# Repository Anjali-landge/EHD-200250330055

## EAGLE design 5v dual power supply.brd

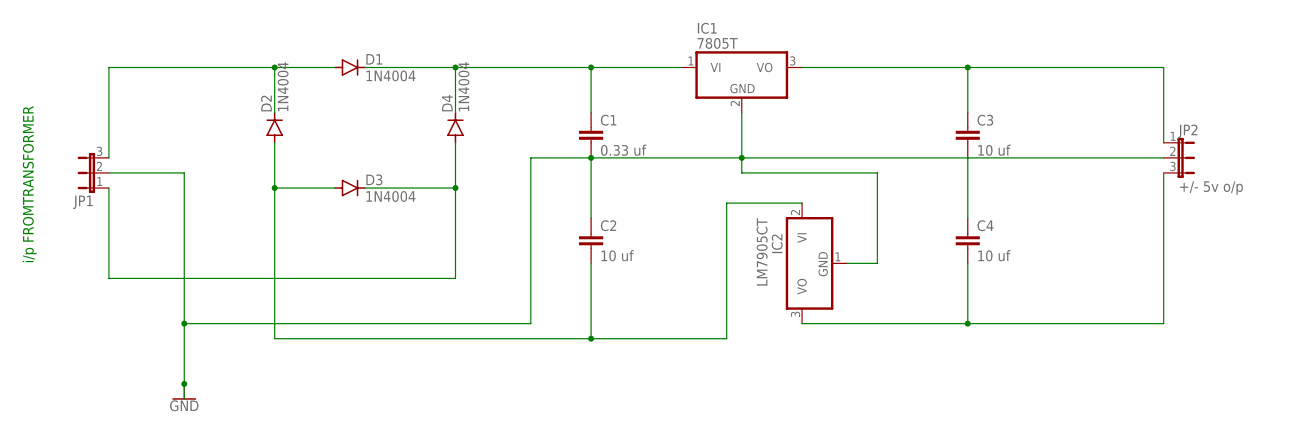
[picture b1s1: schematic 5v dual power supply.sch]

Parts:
C1: 0.33 uf; C2.5-3
C2, C3, C4: 10 uf; C2.5-3
D1, D2, D3, D4: 1N4004; DO41-10
IC1: 7805T; TO220H
IC2: LM7905CT; TO220H
JP1: JP2E; JP2
JP2: +/- 5v o/p; JP2

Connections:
GND: C1.2, C2.1, IC1.2 (GND), IC2.1 (GND), JP1.2, JP2.2
unnamed: C1.1, D1.C, D4.C, IC1.1 (VI)
unnamed: D3.C, D4.A, JP1.1
unnamed: D1.A, D2.C, JP1.3
unnamed: C2.2, D2.A, D3.A, IC2.2 (VI)
unnamed: C3.1, IC1.3 (VO), JP2.1
unnamed: C3.2, C4.1
unnamed: C4.2, IC2.3 (VO), JP2.3

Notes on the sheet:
i/p FROMTRANSFORMER

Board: 2 copper layers, 12 parts (0 on the bottom side), 8 nets, no tracks yet.

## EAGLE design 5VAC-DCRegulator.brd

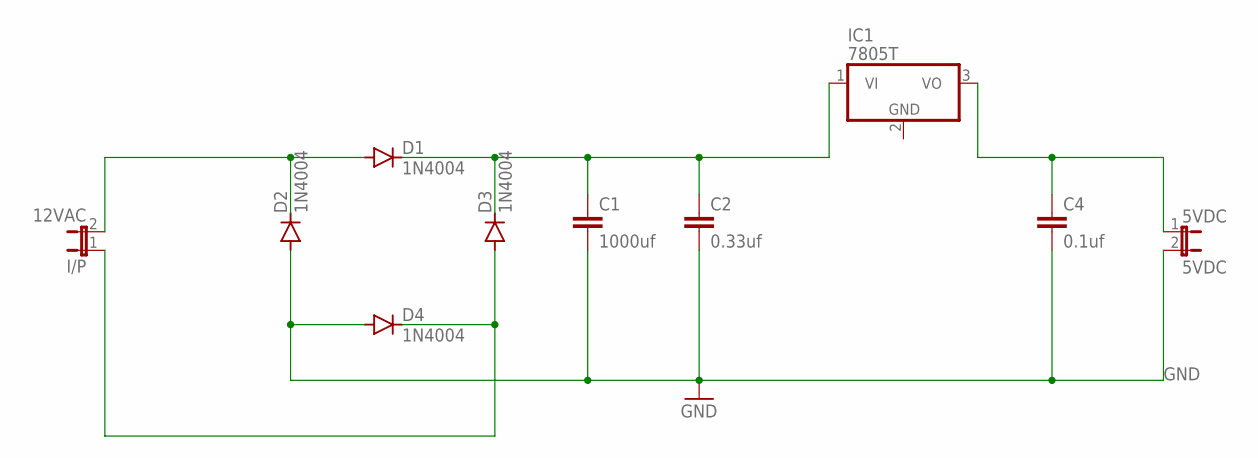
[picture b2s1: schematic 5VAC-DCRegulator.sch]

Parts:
5VDC: 5VDC; JP1
C1: 1000uf; C2.5-3
C2: 0.33uf; C2.5-3
C4: 0.1uf; C2.5-3
D1, D2, D3, D4: 1N4004; DO41-10
I/P: 12VAC; JP1
IC1: 7805T; TO220H

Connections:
GND: 5VDC.2, C1.2, C2.2, C4.2, D2.A, D4.A
unnamed: D1.A, D2.C, I/P.2
unnamed: C1.1, C2.1, D1.C, D3.C, IC1.1 (VI)
unnamed: D3.A, D4.C, I/P.1
unnamed: 5VDC.1, C4.1, IC1.3 (VO)

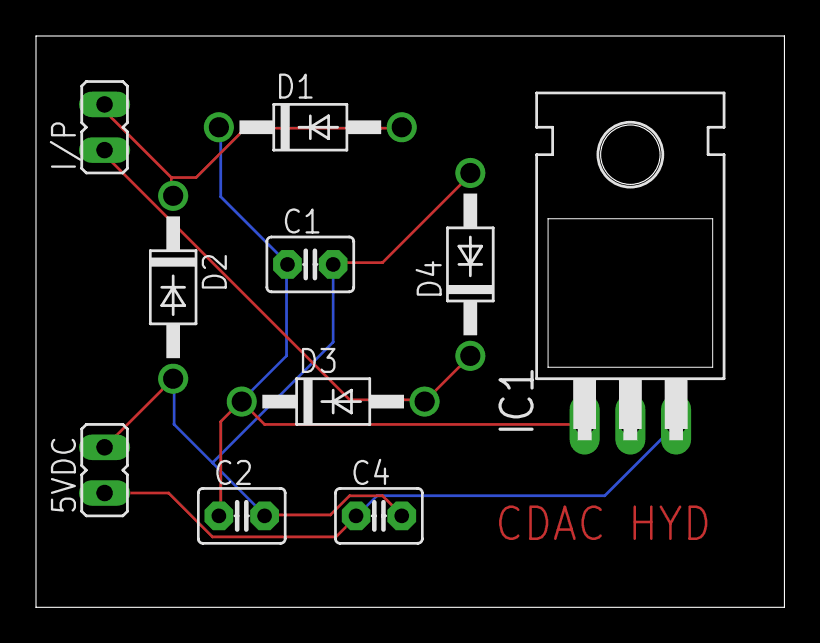
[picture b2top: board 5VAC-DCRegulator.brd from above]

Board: 2 copper layers, 41.6 x 31.7 mm, 10 parts (0 on the bottom side), 5 nets.

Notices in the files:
parts and their libraries:
SparkFun-PowerSymbols: Licensing: Creative Commons ShareAlike 4.0 International - https://creativecommons.org/licenses/by-sa/4.0
